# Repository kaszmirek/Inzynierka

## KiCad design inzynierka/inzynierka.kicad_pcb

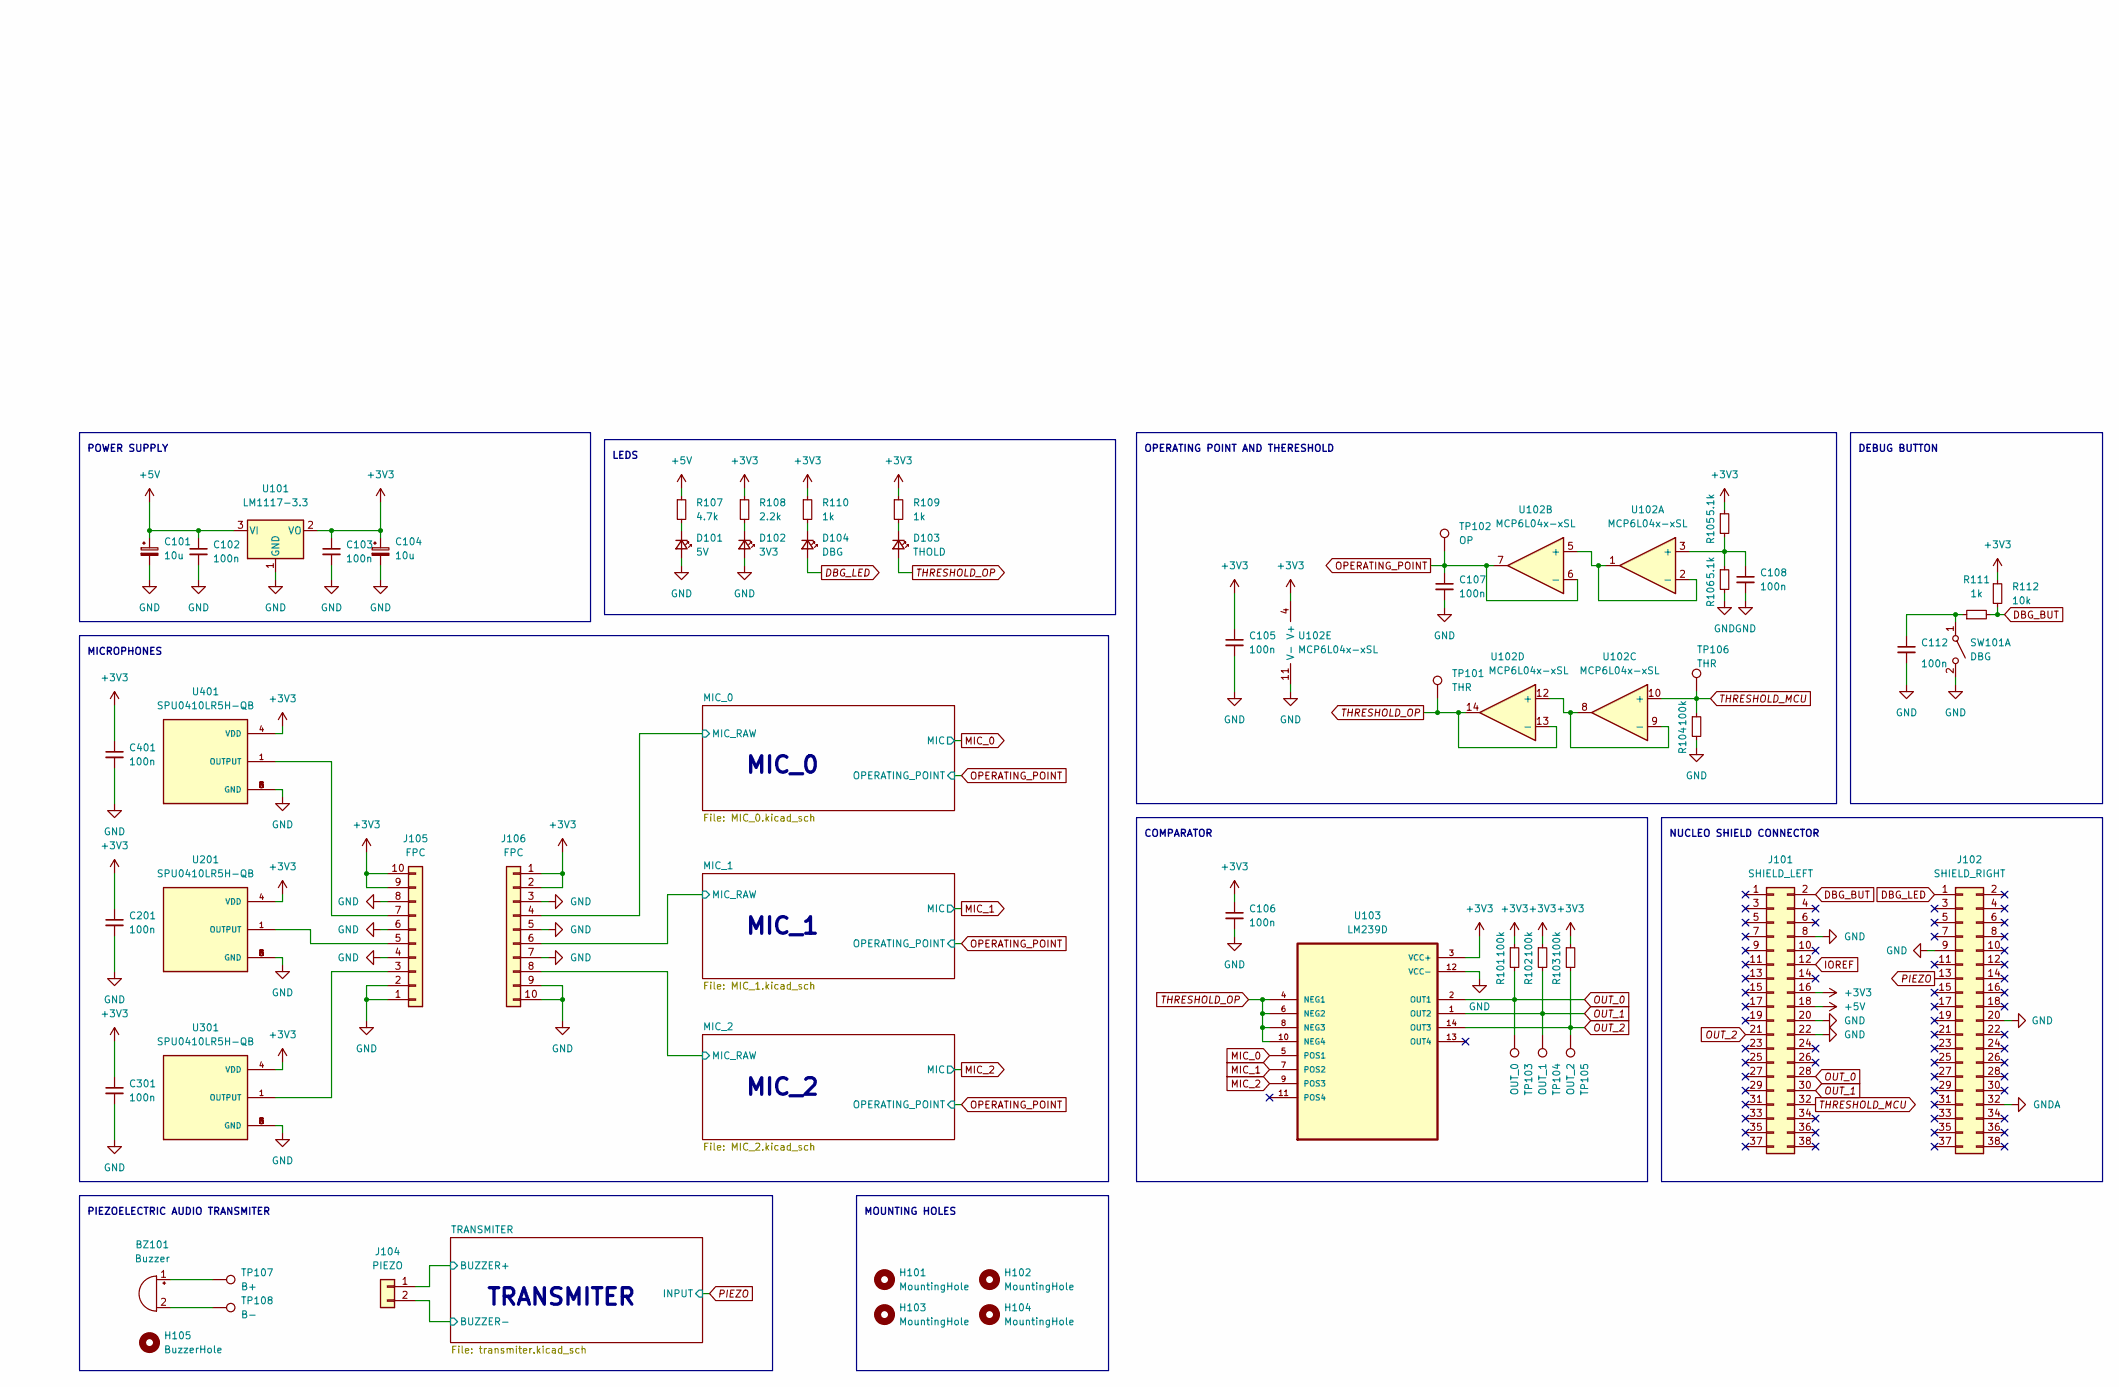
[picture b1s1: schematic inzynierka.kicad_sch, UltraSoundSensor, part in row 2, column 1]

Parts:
BZ101: Buzzer; Buzzer_15x7.5RM7.6
C101, C104: 10u; CP_Elec_4x3
C102, C103, C105, C106, C107, C108, C112, C201, C301, C401: 100n; C_0603_1608Metric
D101: 5V; LED_0603_1608Metric
D102: 3V3; LED_0603_1608Metric
D103: THOLD; LED_0603_1608Metric
D104: DBG; LED_0603_1608Metric
H101, H102, H103, H104: MountingHole; MountingHole_3.2mm_M3
H105: BuzzerHole; MountingHole_2.2mm_M2
J101: SHIELD_LEFT; PinSocket_2x19_P2.54mm_Vertical
J102: SHIELD_RIGHT; PinSocket_2x19_P2.54mm_Vertical
J104: PIEZO; PinHeader_1x02_P2.54mm_Vertical
J105, J106: FPC; Hirose_FH12-10S-0.5SH_1x10-1MP_P0.50mm_Horizontal
R101, R102, R103, R104: 100k; R_0603_1608Metric
R105, R106: 5.1k; R_0603_1608Metric
R107: 4.7k; R_0603_1608Metric
R108: 2.2k; R_0603_1608Metric
R109, R110, R111: 1k; R_0603_1608Metric
R112: 10k; R_0603_1608Metric
SW101: DBG; SW_SPST_B3S-1000
TP101, TP106: THR; TestPoint_Pad_D1.0mm
TP102: OP; TestPoint_Pad_D1.0mm
TP103: OUT_0; TestPoint_Pad_D1.0mm
TP104: OUT_1; TestPoint_Pad_D1.0mm
TP105: OUT_2; TestPoint_Pad_D1.0mm
TP107: B+; TestPoint_Pad_D2.0mm
TP108: B-; TestPoint_Pad_D2.0mm
U101: LM1117-3.3; SOT-223-3_TabPin2
U102: MCP6L04x-xSL; SOIC-14_3.9x8.7mm_P1.27mm
U103: LM239D; SOIC-14_3.9x8.7mm_P1.27mm
U201, U301, U401: SPU0410LR5H-QB; PARTREV H

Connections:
+3V3: C103.1, C104.1, C105.1, C106.1, C201.1, C301.1, C401.1, J101.16, J105.9, J105.10, J106.1, J106.2, R101.1, R102.1, R103.1, R105.1, R108.1, R109.1, R110.1, R112.1, U101.2 (VO), U102.4 (V+), U103.3 (VCC+), U201.4 (VDD), U301.4 (VDD), U401.4 (VDD); also elsewhere on the board
+5V: C101.1, C102.1, J101.18, R107.1, U101.3 (VI); also elsewhere on the board
/MIC_0/MIC_RAW: J106.4; also elsewhere on the board
/MIC_1/MIC_RAW: J106.6; also elsewhere on the board
/MIC_2/MIC_RAW: J106.8; also elsewhere on the board
/TRANSMITER/BUZZER+: J104.1; also elsewhere on the board
/TRANSMITER/BUZZER-: J104.2; also elsewhere on the board
DBG_BUT: J101.2, R111.2, R112.2
DBG_LED: D104.2 (A), J102.1
GND: C101.2, C102.2, C103.2, C104.2, C105.2, C106.2, C107.2, C108.2, C112.2, C201.2, C301.2, C401.2, D101.2 (A), D102.2 (A), J101.8, J101.20, J101.22, J102.9, J102.20, J105.1, J105.2, J105.4, J105.6, J105.8, J106.3, J106.5, J106.7, J106.9, J106.10, R104.2, R106.2, SW101.2 (B), U101.1 (GND), U102.11 (V-), U103.12 (VCC-), U201.2 (GND), U201.3 (GND), U201.5 (GND), U201.6 (GND), U301.2 (GND), U301.3 (GND), U301.5 (GND), U301.6 (GND), U401.2 (GND), U401.3 (GND), U401.5 (GND), U401.6 (GND); also elsewhere on the board
GNDA: J102.32
IOREF: J101.12
MIC_0: U103.5 (POS1); also elsewhere on the board
MIC_1: U103.7 (POS2); also elsewhere on the board
MIC_2: U103.9 (POS3); also elsewhere on the board
unnamed: BZ101.1 (-), TP107.1
unnamed: BZ101.2 (+), TP108.1
unnamed: C108.1, R105.2, R106.1, U102.3 (+)
unnamed: C112.1, R111.1, SW101.1 (A)
unnamed: D101.1 (K), R107.2
unnamed: D102.1 (K), R108.2
unnamed: D103.1 (K), R109.2
unnamed: D104.1 (K), R110.2
unnamed: J105.3, U301.1 (OUTPUT)
unnamed: J105.5, U201.1 (OUTPUT)
unnamed: J105.7, U401.1 (OUTPUT)
unnamed: U102.1, U102.2 (-), U102.5 (+)
unnamed: U102.8, U102.9 (-), U102.12 (+)
OPERATING_POINT: C107.1, TP102.1, U102.6 (-), U102.7; also elsewhere on the board
OUT_0: J101.28, R101.2, TP103.1, U103.2 (OUT1)
OUT_1: J101.30, R102.2, TP104.1, U103.1 (OUT2)
OUT_2: J101.21, R103.2, TP105.1, U103.14 (OUT3)
PIEZO: J102.13; also elsewhere on the board
THRESHOLD_MCU: J101.32, R104.1, TP106.1, U102.10 (+)
THRESHOLD_OP: D103.2 (A), TP101.1, U102.13 (-), U102.14, U103.4 (NEG1), U103.6 (NEG2), U103.8 (NEG3), U103.10 (NEG4)

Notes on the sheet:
NUCLEO SHIELD CONNECTOR
MICROPHONES
COMPARATOR
PIEZOELECTRIC AUDIO TRANSMITER
OPERATING POINT AND THERESHOLD
POWER SUPPLY
DEBUG BUTTON
TRANSMITER
MIC_1
MIC_0
LEDS
MOUNTING HOLES
MIC_2

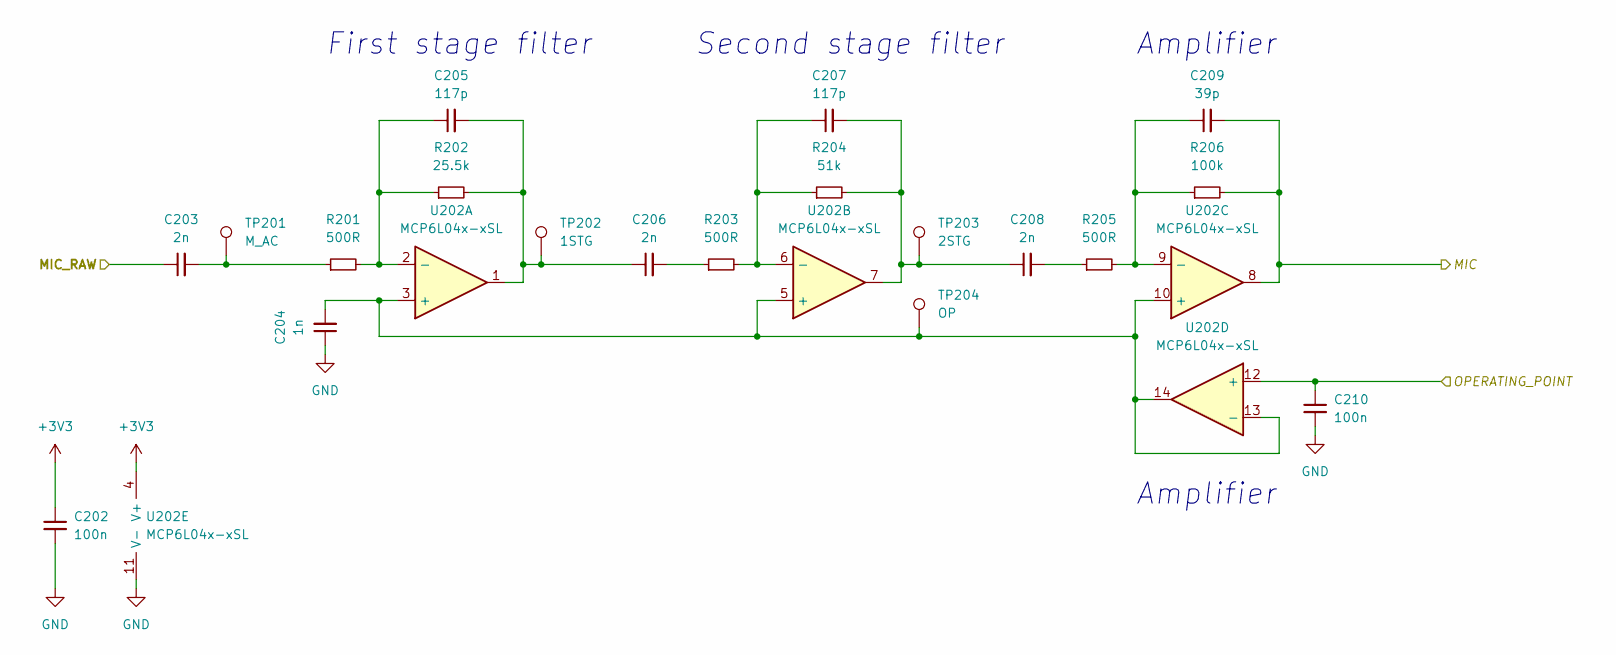
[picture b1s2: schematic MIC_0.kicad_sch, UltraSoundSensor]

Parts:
C202, C210: 100n; C_0603_1608Metric
C203, C206, C208: 2n; C_0603_1608Metric
C204: 1n; C_0603_1608Metric
C205, C207: 117p; C_0603_1608Metric
C209: 39p; C_0603_1608Metric
R201, R203, R205: 500R; R_0603_1608Metric
R202: 25.5k; R_0603_1608Metric
R204: 51k; R_0603_1608Metric
R206: 100k; R_0603_1608Metric
TP201: M_AC; TestPoint_Pad_D1.0mm
TP202: 1STG; TestPoint_Pad_D1.0mm
TP203: 2STG; TestPoint_Pad_D1.0mm
TP204: OP; TestPoint_Pad_D1.0mm
U202: MCP6L04x-xSL; SOIC-14_3.9x8.7mm_P1.27mm

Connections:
+3V3: C202.1, U202.4 (V+); also elsewhere on the board
/MIC_0/MIC_RAW: C203.1; also elsewhere on the board
GND: C202.2, C204.1, C210.2, U202.11 (V-); also elsewhere on the board
MIC_0: C209.2, R206.2, U202.8; also elsewhere on the board
unnamed: C203.2, R201.1, TP201.1
unnamed: C204.2, TP204.1, U202.3 (+), U202.5 (+), U202.10 (+), U202.13 (-), U202.14
unnamed: C205.1, R201.2, R202.1, U202.2 (-)
unnamed: C205.2, C206.1, R202.2, TP202.1, U202.1
unnamed: C206.2, R203.1
unnamed: C207.1, R203.2, R204.1, U202.6 (-)
unnamed: C207.2, C208.1, R204.2, TP203.1, U202.7
unnamed: C208.2, R205.1
unnamed: C209.1, R205.2, R206.1, U202.9 (-)
OPERATING_POINT: C210.1, U202.12 (+); also elsewhere on the board

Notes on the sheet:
Amplifier
First stage filter
Second stage filter

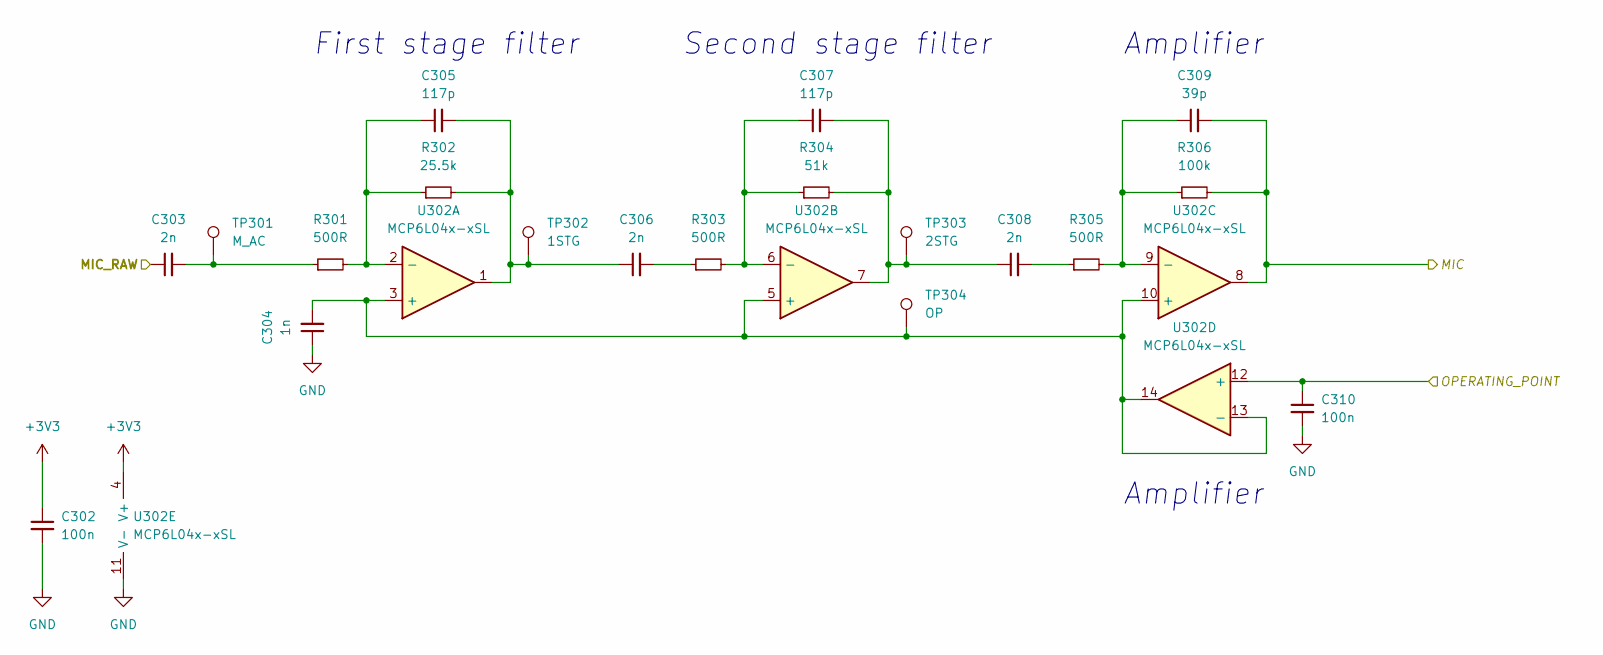
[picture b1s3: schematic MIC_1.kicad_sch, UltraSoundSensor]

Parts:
C302, C310: 100n; C_0603_1608Metric
C303, C306, C308: 2n; C_0603_1608Metric
C304: 1n; C_0603_1608Metric
C305, C307: 117p; C_0603_1608Metric
C309: 39p; C_0603_1608Metric
R301, R303, R305: 500R; R_0603_1608Metric
R302: 25.5k; R_0603_1608Metric
R304: 51k; R_0603_1608Metric
R306: 100k; R_0603_1608Metric
TP301: M_AC; TestPoint_Pad_D1.0mm
TP302: 1STG; TestPoint_Pad_D1.0mm
TP303: 2STG; TestPoint_Pad_D1.0mm
TP304: OP; TestPoint_Pad_D1.0mm
U302: MCP6L04x-xSL; SOIC-14_3.9x8.7mm_P1.27mm

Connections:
+3V3: C302.1, U302.4 (V+); also elsewhere on the board
/MIC_1/MIC_RAW: C303.1; also elsewhere on the board
GND: C302.2, C304.1, C310.2, U302.11 (V-); also elsewhere on the board
MIC_1: C309.2, R306.2, U302.8; also elsewhere on the board
unnamed: C303.2, R301.1, TP301.1
unnamed: C304.2, TP304.1, U302.3 (+), U302.5 (+), U302.10 (+), U302.13 (-), U302.14
unnamed: C305.1, R301.2, R302.1, U302.2 (-)
unnamed: C305.2, C306.1, R302.2, TP302.1, U302.1
unnamed: C306.2, R303.1
unnamed: C307.1, R303.2, R304.1, U302.6 (-)
unnamed: C307.2, C308.1, R304.2, TP303.1, U302.7
unnamed: C308.2, R305.1
unnamed: C309.1, R305.2, R306.1, U302.9 (-)
OPERATING_POINT: C310.1, U302.12 (+); also elsewhere on the board

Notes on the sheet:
Amplifier
First stage filter
Second stage filter

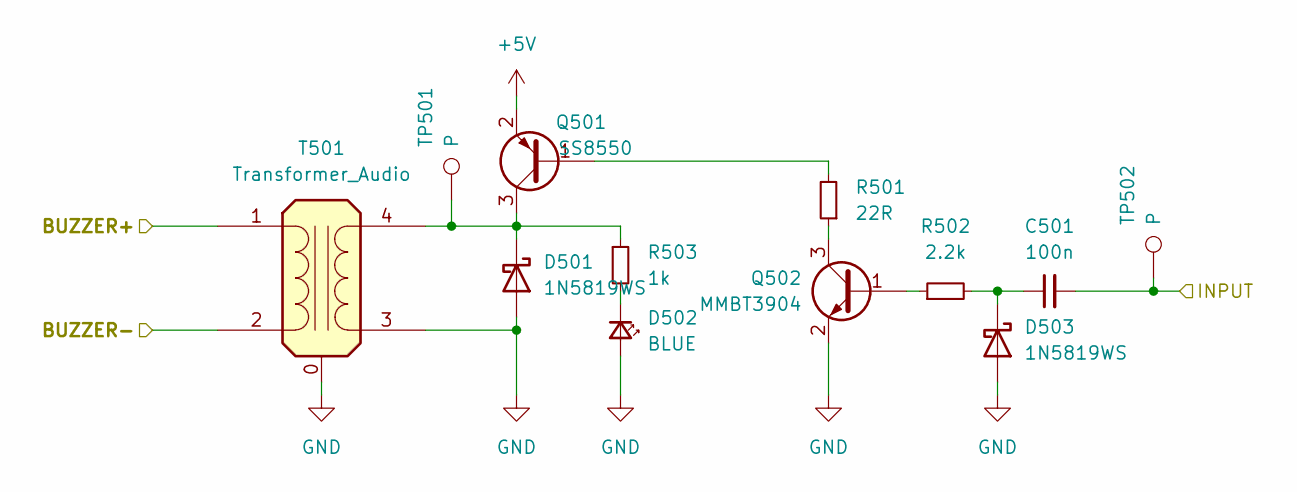
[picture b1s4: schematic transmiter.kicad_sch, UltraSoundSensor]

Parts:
C501: 100n; C_0603_1608Metric
D501, D503: 1N5819WS; D_SOD-323
D502: BLUE; LED_0603_1608Metric
Q501: SS8550; SOT-23
Q502: MMBT3904; SOT-23
R501: 22R; R_0603_1608Metric
R502: 2.2k; R_0603_1608Metric
R503: 1k; R_0603_1608Metric
T501: Transformer_Audio; Transformer_shielded_8x13.5
TP501, TP502: P; TestPoint_Pad_D1.0mm

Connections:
+5V: Q501.2 (E); also elsewhere on the board
/TRANSMITER/BUZZER+: T501.1 (AA); also elsewhere on the board
/TRANSMITER/BUZZER-: T501.2 (AB); also elsewhere on the board
GND: D501.2 (A), D502.2 (A), D503.2 (A), Q502.2 (E), T501.0, T501.3 (SA); also elsewhere on the board
unnamed: C501.1, D503.1 (K), R502.2
unnamed: D501.1 (K), Q501.3 (C), R503.1, T501.4 (SB), TP501.1
unnamed: D502.1 (K), R503.2
unnamed: Q501.1 (B), R501.2
unnamed: Q502.1 (B), R502.1
unnamed: Q502.3 (C), R501.1
PIEZO: C501.2, TP502.1; also elsewhere on the board

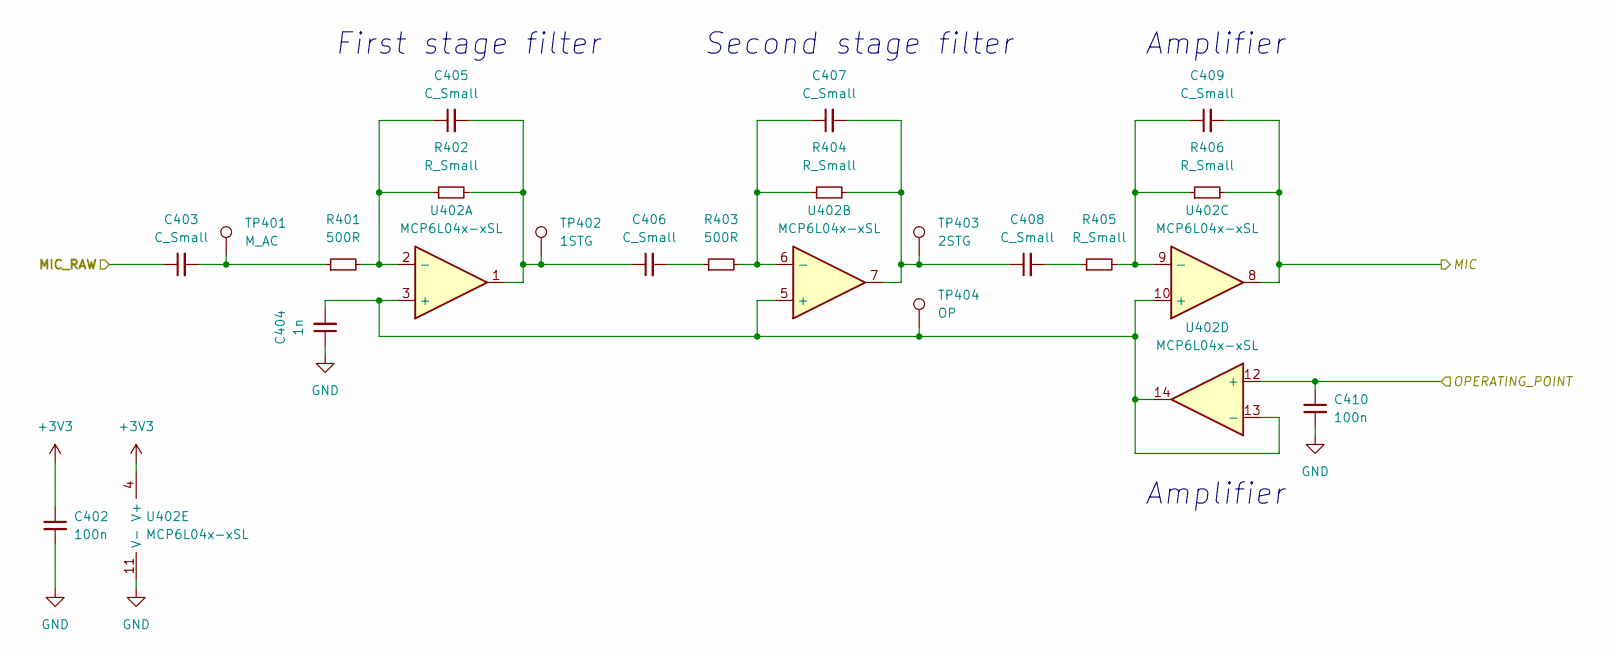
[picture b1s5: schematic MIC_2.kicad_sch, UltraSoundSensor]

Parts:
C402, C410: 100n; C_0603_1608Metric
C403, C405, C406, C407, C408, C409: C_Small; C_0603_1608Metric
C404: 1n; C_0603_1608Metric
R401, R403: 500R; R_0603_1608Metric
R402, R404, R405, R406: R_Small; R_0603_1608Metric
TP401: M_AC; TestPoint_Pad_D1.0mm
TP402: 1STG; TestPoint_Pad_D1.0mm
TP403: 2STG; TestPoint_Pad_D1.0mm
TP404: OP; TestPoint_Pad_D1.0mm
U402: MCP6L04x-xSL; SOIC-14_3.9x8.7mm_P1.27mm

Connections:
+3V3: C402.1, U402.4 (V+); also elsewhere on the board
/MIC_2/MIC_RAW: C403.1; also elsewhere on the board
GND: C402.2, C404.1, C410.2, U402.11 (V-); also elsewhere on the board
MIC_2: C409.2, R406.2, U402.8; also elsewhere on the board
unnamed: C403.2, R401.1, TP401.1
unnamed: C404.2, TP404.1, U402.3 (+), U402.5 (+), U402.10 (+), U402.13 (-), U402.14
unnamed: C405.1, R401.2, R402.1, U402.2 (-)
unnamed: C405.2, C406.1, R402.2, TP402.1, U402.1
unnamed: C406.2, R403.1
unnamed: C407.1, R403.2, R404.1, U402.6 (-)
unnamed: C407.2, C408.1, R404.2, TP403.1, U402.7
unnamed: C408.2, R405.1
unnamed: C409.1, R405.2, R406.1, U402.9 (-)
OPERATING_POINT: C410.1, U402.12 (+); also elsewhere on the board

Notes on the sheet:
Amplifier
First stage filter
Second stage filter

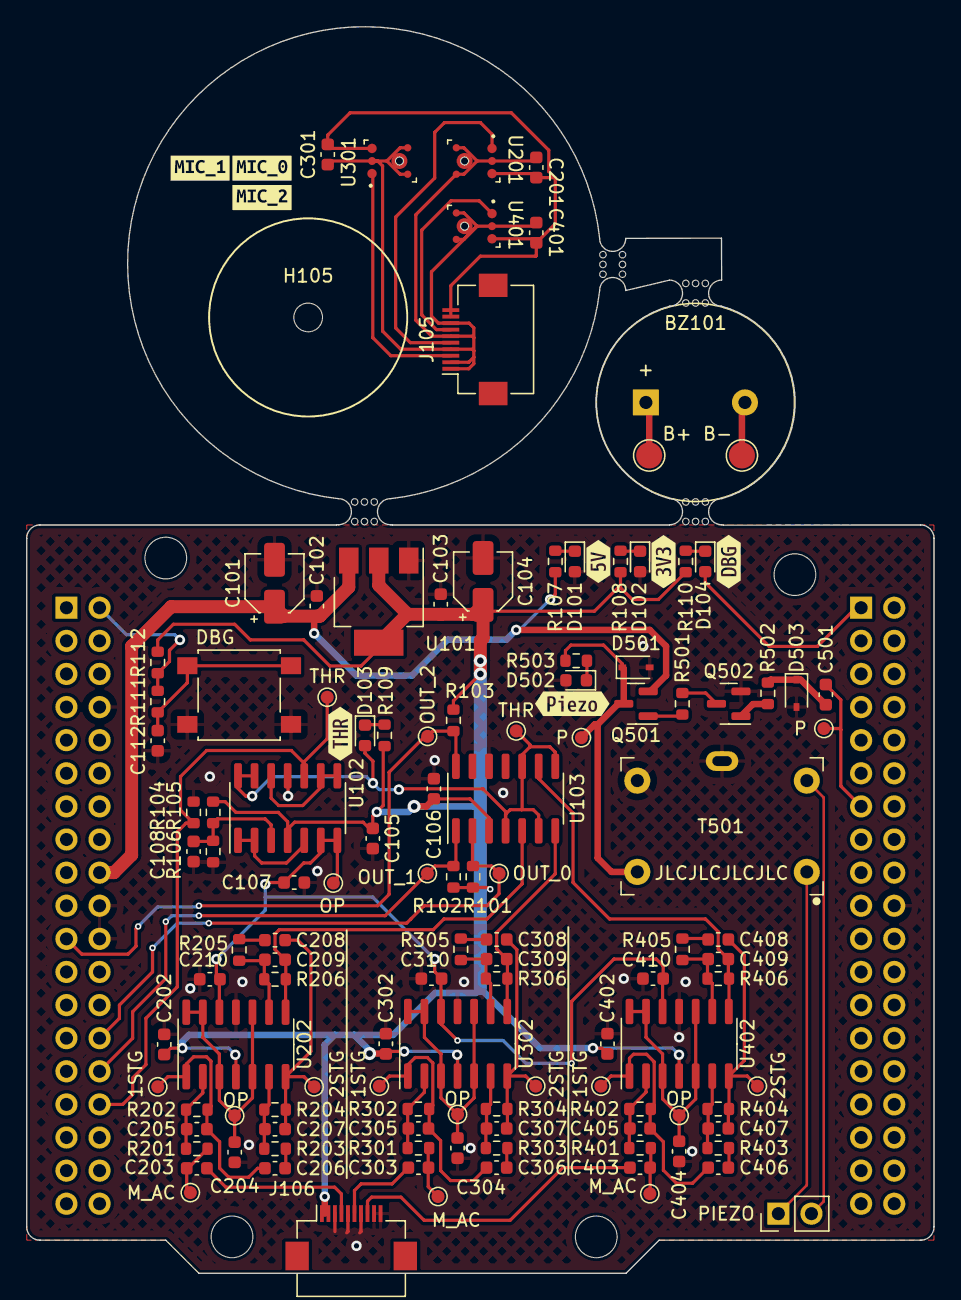
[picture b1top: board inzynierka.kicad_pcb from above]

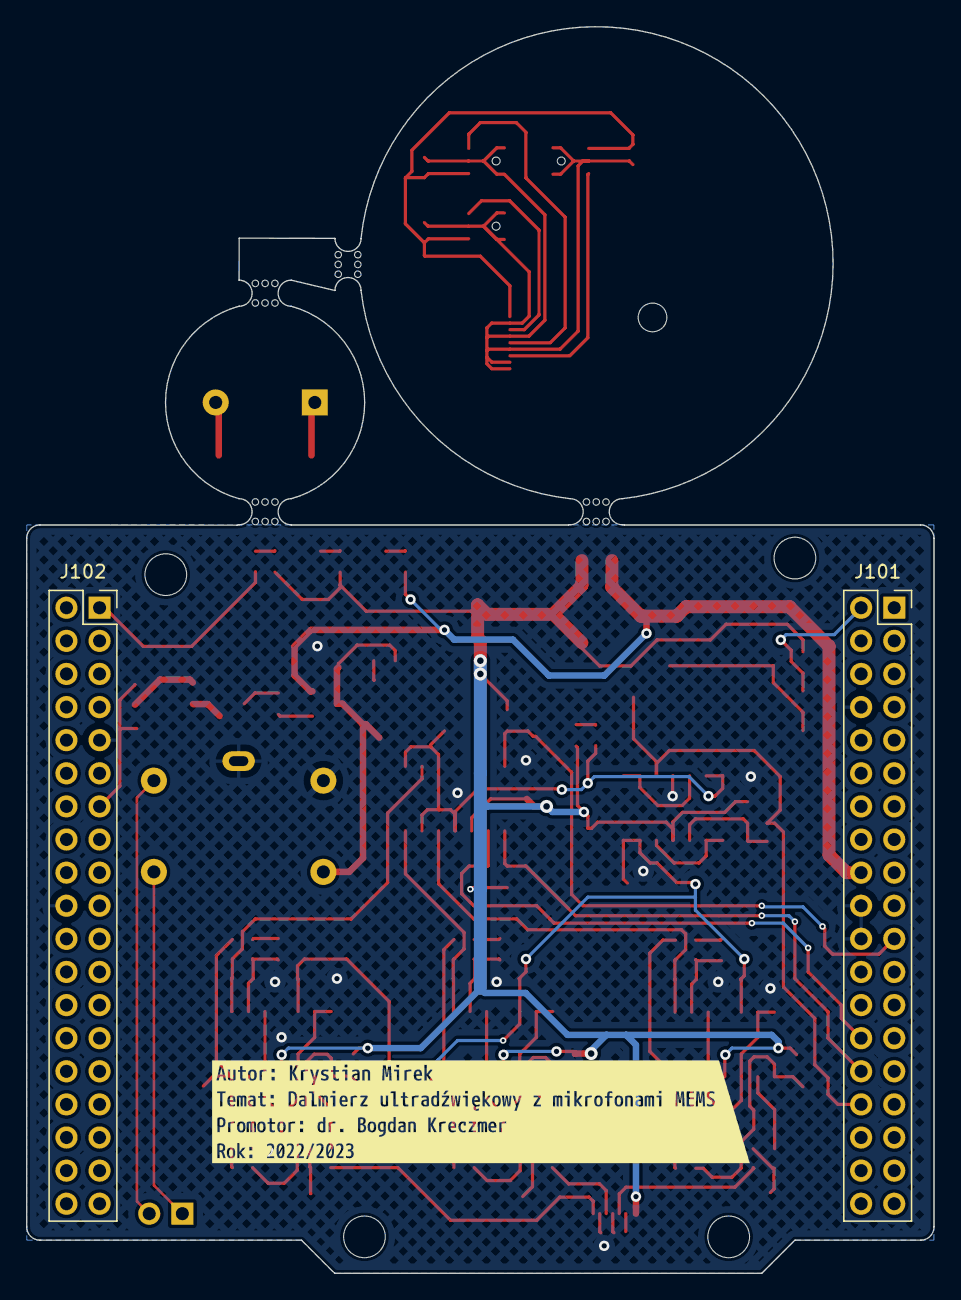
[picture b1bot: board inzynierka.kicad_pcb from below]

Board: 2 copper layers, 69.6 x 95.6 mm, 139 parts (3 on the bottom side), 66 nets.

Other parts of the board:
kibuzzard-6361BCC4: G***; kibuzzard-6361BCC4
kibuzzard-6361BD6E: G***; kibuzzard-6361BD6E
kibuzzard-6361BD58: G***; kibuzzard-6361BD58
kibuzzard-6361BD82: G***; kibuzzard-6361BD82
kibuzzard-6361C7A3: G***; kibuzzard-6361C7A3
kibuzzard-6361C7DF: G***; kibuzzard-6361C7DF
kibuzzard-636196D3: G***; kibuzzard-636196D3
kibuzzard-636196F7: G***; kibuzzard-636196F7
kibuzzard-636196FE: G***; kibuzzard-636196FE
mouse-bite-2mm-slot, mouse-bite-2mm-slot#2, mouse-bite-2mm-slot#3, mouse-bite-2mm-slot#4: VAL**; mouse-bite-2mm-slot

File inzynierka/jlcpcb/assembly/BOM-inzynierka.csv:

Comment,Designator,Footprint,LCSC
100n,"C102,C103,C105,C106,C107,C108,C112,C201,C202,C210,C301,C302,C310,C401,C402,C410,C501",C_0603_1608Metric,C14663
1n,"C204,C304,C404",C_0603_1608Metric,C1588
2n,"C203,C206,C208,C303,C306,C308,C403,C406,C408",C_0603_1608Metric,C1604
1N5819WS,"D501,D503",D_SOD-323,C191023
MMBT3904,Q502,SOT-23,C20526
1k,"R109,R110,R111,R503",R_0603_1608Metric,C21190
5V,"D101,D102",LED_0603_1608Metric,C2286
22R,R501,R_0603_1608Metric,C22950
4.7k,R107,R_0603_1608Metric,C23162
5.1k,"R105,R106",R_0603_1608Metric,C23186
500R,"R201,R203,R205,R301,R303,R305,R401,R403,R405",R_0603_1608Metric,C23193
51k,"R204,R304,R404",R_0603_1608Metric,C23196
25.5k,"R202,R302,R402",R_0603_1608Metric,C23352
100k,"R101,R102,R103,R104,R206,R306,R406",R_0603_1608Metric,C25803
10k,R112,R_0603_1608Metric,C25804
2.2k,"R108,R502",R_0603_1608Metric,C4190
LM1117-3.3,U101,SOT-223-3_TabPin2,C6186
MCP6L04x-xSL,"U102,U202,U302,U402",SOIC-14_3.9x8.7mm_P1.27mm,C626833
FPC,"J105,J106",Hirose_FH12-10S-0.5SH_1x10-1MP_P0.50mm_Horizontal,C709365
THOLD,D103,LED_0603_1608Metric,C72038
BLUE,D502,LED_0603_1608Metric,C72041
DBG,D104,LED_0603_1608Metric,C72043
LM239D,U103,SOIC-14_3.9x8.7mm_P1.27mm,C7927
SS8550,Q501,SOT-23,C8542
DBG,SW101,SW_SPST_TL3342,

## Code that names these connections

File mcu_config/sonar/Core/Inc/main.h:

/* USER CODE BEGIN Header */
/**
  ******************************************************************************
  * @file           : main.h
  * @brief          : Header for main.c file.
  *                   This file contains the common defines of the application.
  ******************************************************************************
  * @attention
  *
  * <h2><center>&copy; Copyright (c) 2022 STMicroelectronics.
  * All rights reserved.</center></h2>
  *
  * This software component is licensed by ST under BSD 3-Clause license,
  * the "License"; You may not use this file except in compliance with the
  * License. You may obtain a copy of the License at:
  *                        opensource.org/licenses/BSD-3-Clause
  *
  ******************************************************************************
  */
/* USER CODE END Header */

/* Define to prevent recursive inclusion -------------------------------------*/
#ifndef __MAIN_H
#define __MAIN_H

#ifdef __cplusplus
extern "C" {
#endif

/* Includes ------------------------------------------------------------------*/
#include "stm32l4xx_hal.h"

/* Private includes ----------------------------------------------------------*/
/* USER CODE BEGIN Includes */

/* USER CODE END Includes */

/* Exported types ------------------------------------------------------------*/
/* USER CODE BEGIN ET */

/* USER CODE END ET */

/* Exported constants --------------------------------------------------------*/
/* USER CODE BEGIN EC */

/* USER CODE END EC */

/* Exported macro ------------------------------------------------------------*/
/* USER CODE BEGIN EM */

/* USER CODE END EM */

/* Exported functions prototypes ---------------------------------------------*/
void Error_Handler(void);

/* USER CODE BEGIN EFP */

/* USER CODE END EFP */

/* Private defines -----------------------------------------------------------*/
#define B1_Pin GPIO_PIN_13
#define B1_GPIO_Port GPIOC
#define MIC_0_Pin GPIO_PIN_0
#define MIC_0_GPIO_Port GPIOA
#define MIC_1_Pin GPIO_PIN_1
#define MIC_1_GPIO_Port GPIOA
#define USART_TX_Pin GPIO_PIN_2
#define USART_TX_GPIO_Port GPIOA
#define USART_RX_Pin GPIO_PIN_3
#define USART_RX_GPIO_Port GPIOA
#define THR_Pin GPIO_PIN_4
#define THR_GPIO_Port GPIOA
#define LD2_Pin GPIO_PIN_5
#define LD2_GPIO_Port GPIOA
#define PIEZO_Pin GPIO_PIN_6
#define PIEZO_GPIO_Port GPIOA
#define DBG_LED_Pin GPIO_PIN_9
#define DBG_LED_GPIO_Port GPIOC
#define TMS_Pin GPIO_PIN_13
#define TMS_GPIO_Port GPIOA
#define TCK_Pin GPIO_PIN_14
#define TCK_GPIO_Port GPIOA
#define DBG_BUT_Pin GPIO_PIN_11
#define DBG_BUT_GPIO_Port GPIOC
#define SWO_Pin GPIO_PIN_3
#define SWO_GPIO_Port GPIOB
#define MIC_2_Pin GPIO_PIN_7
#define MIC_2_GPIO_Port GPIOB
/* USER CODE BEGIN Private defines */

/* USER CODE END Private defines */

#ifdef __cplusplus
}
#endif

#endif /* __MAIN_H */

/************************ (C) COPYRIGHT STMicroelectronics *****END OF FILE****/

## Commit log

2022-10-29 kicad
2022-10-29 docs
2022-10-29 shield shape
2022-10-30 nowy folder
2022-11-02 skonczone pcb
2022-11-02 production files
2022-11-07 poprawione gerbery
2022-11-07 poprawione gerbery na pewno
2022-11-13 cleanup
2022-11-27 progress in thesis
2022-11-30 another progress in thesis
2022-12-05 little changes after promoter remarks
2022-12-12 minor thesis changes
2022-12-20 progress before last consultation
2022-12-20 chapter 9
2022-12-22 gotowa praca dyplomowa
2024-09-20 added presentation
